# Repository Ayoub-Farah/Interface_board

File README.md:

# Obsidian

## Description

Obsidian is a FPGA carrier board in development, designed to interface with ADC and DAC devices,
either stand-alone or as an I/O expansion board for [Marble](https://github.com/BerkeleyLab/Marble).

The design files here were created with [KiCad](https://www.kicad.org/) version 9.0.0-rc3.

## Major Parts

- Xilinx XC7A50T-1CSG325C FPGA

## Credits

## License

---

## Project status

### Included features

- [ ] Arduino shield compatible, like the Digilent Arty
- [ ] SPI flash boot
- [ ] DDR3 memory chip
- [ ] FTDI USB interface
- [ ] 2 direct LEDs
- [ ] 1 GigE port (PoE?)
- [ ] 6 Pmod ports (3.3V)
- [ ] MS5351M or SI5351A or similar for GTP frequency reference
- [ ] USB-C (single USB cable)
- [ ] 4 x SFP
- [ ] I2C or 1-Wire chip for serial number / ROM
- [ ] White Rabbit compatibility

### High speed links

The 7A50T-1CSG325C has 4 x GTP lanes, capable of 3.75 Gbaud.
The primary use-case involves attaching one of those to a Marble over fiber.

The two MGTREFCLK signals are the direct White-Rabbit 125 MHz TCVCXO
and the configurable MS5351M output.

### Wishlist

- [ ] Standardized board size for good case options: Mini-ATX (150 x 150 mm)? Pico-ATX?

### User I/O Pins
- 48 pins for 6 x Pmod
- 49 pins for DDR3 (equivalent to Arty and Marble-Mini)
- 13 pins for RGMII (including reset pin)
- 2 Ethernet PHY MDIO
- 4 pins for White Rabbit DAC (can attach LEDs to 2 x SYNC pins?)
- 1 or more clock input (not counting MGTREFCLK)
- 2 pins for I2C
- 14 pins for Arduino digital IO
- 8 pins for Arduino 4 analog channels
- 2 pins USB UART
- 3 pins SPI flash boot (not counting CCLK in bank 0)

total 146 so far, out of 150 possible with 7A50T-1CSG325C

## Copyright

Obsidian A35 Copyright (c) 2025, The Regents of the University of California, through Lawrence Berkeley National Laboratory (subject to receipt of any required approvals from the U.S. Department of Energy). All rights reserved.

This documentation describes Obsidian A35 and is licensed under the CERN Open Hardware License v 2.0 - Permissive.

NOTICE. This documentation was developed under funding from the U.S. Department of Energy and the U.S. Government consequently retains certain rights. As such, the U.S. Government has been granted for itself and others acting on its behalf a paid-up, nonexclusive, irrevocable, worldwide license in the documentation to reproduce, distribute copies to the public, prepare derivative works, and perform publicly and display publicly, and to permit others to do so.

You may redistribute and modify this documentation under the terms of the CERN OHL v. 2.0 - Permissive (see [CERN-OHL-P-2.0](https://spdx.org/licenses/CERN-OHL-P-2.0.html) for terms and conditions). THIS DOCUMENTATION IS PROVIDED BY THE COPYRIGHT HOLDERS AND CONTRIBUTORS "AS IS" AND ANY EXPRESS OR IMPLIED WARRANTIES, INCLUDING, BUT NOT LIMITED TO, THE IMPLIED WARRANTIES OF MERCHANTABILITY AND FITNESS FOR A PARTICULAR PURPOSE ARE DISCLAIMED. IN NO EVENT SHALL THE COPYRIGHT OWNER OR CONTRIBUTORS BE LIABLE FOR ANY DIRECT, INDIRECT, INCIDENTAL, SPECIAL, EXEMPLARY, OR CONSEQUENTIAL DAMAGES (INCLUDING, BUT NOT LIMITED TO, PROCUREMENT OF SUBSTITUTE GOODS OR SERVICES; LOSS OF USE, DATA, OR PROFITS; OR BUSINESS INTERRUPTION) HOWEVER CAUSED AND ON ANY THEORY OF LIABILITY, WHETHER IN CONTRACT, STRICT LIABILITY, OR TORT (INCLUDING NEGLIGENCE OR OTHERWISE) ARISING IN ANY WAY OUT OF THE USE OF THIS SOFTWARE, EVEN IF ADVISED OF THE POSSIBILITY OF SUCH DAMAGE. Please see the CERN OHL v. 2.0 for applicable conditions.

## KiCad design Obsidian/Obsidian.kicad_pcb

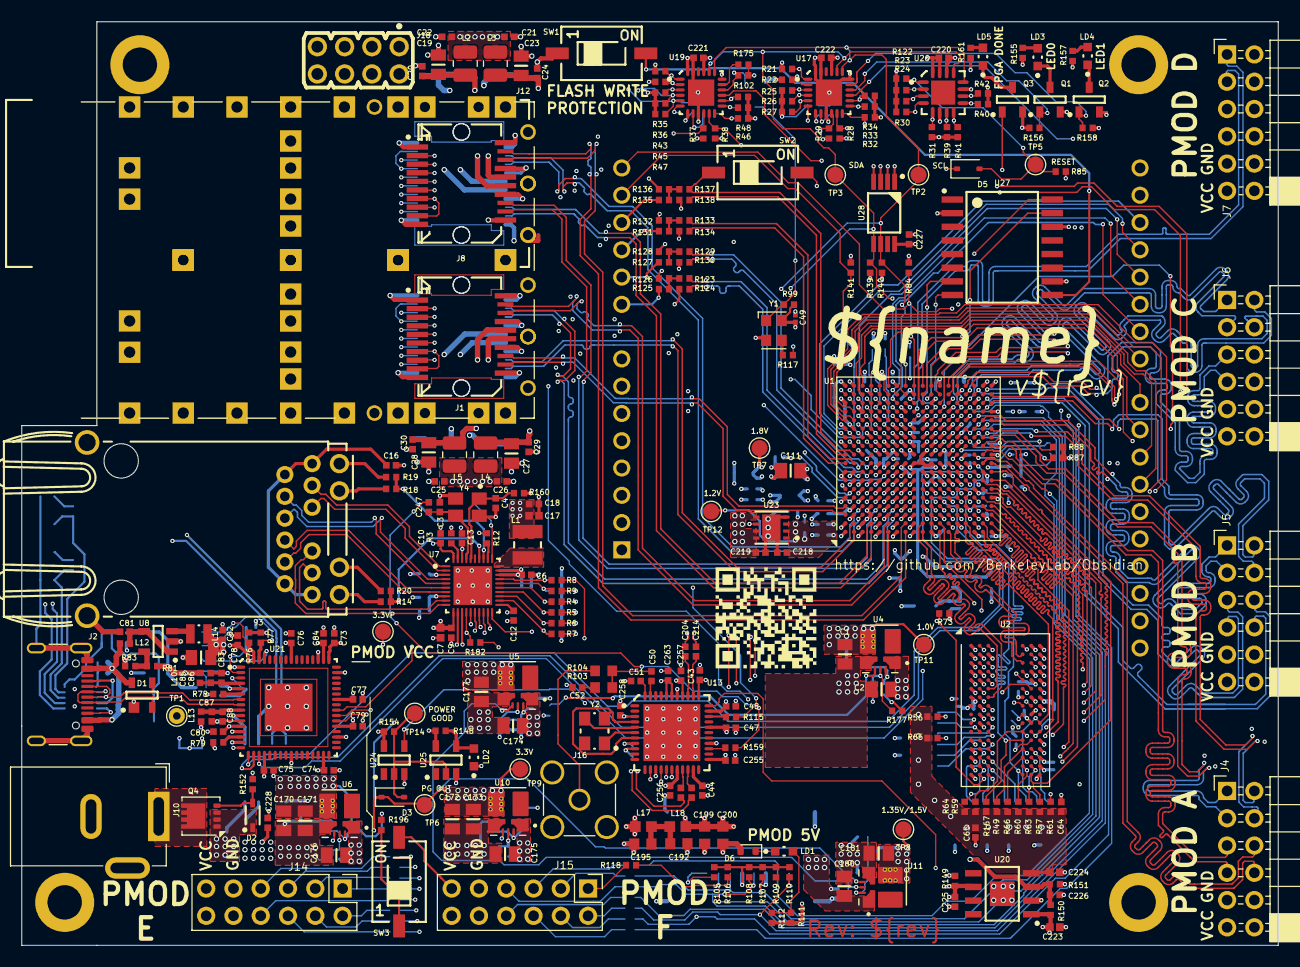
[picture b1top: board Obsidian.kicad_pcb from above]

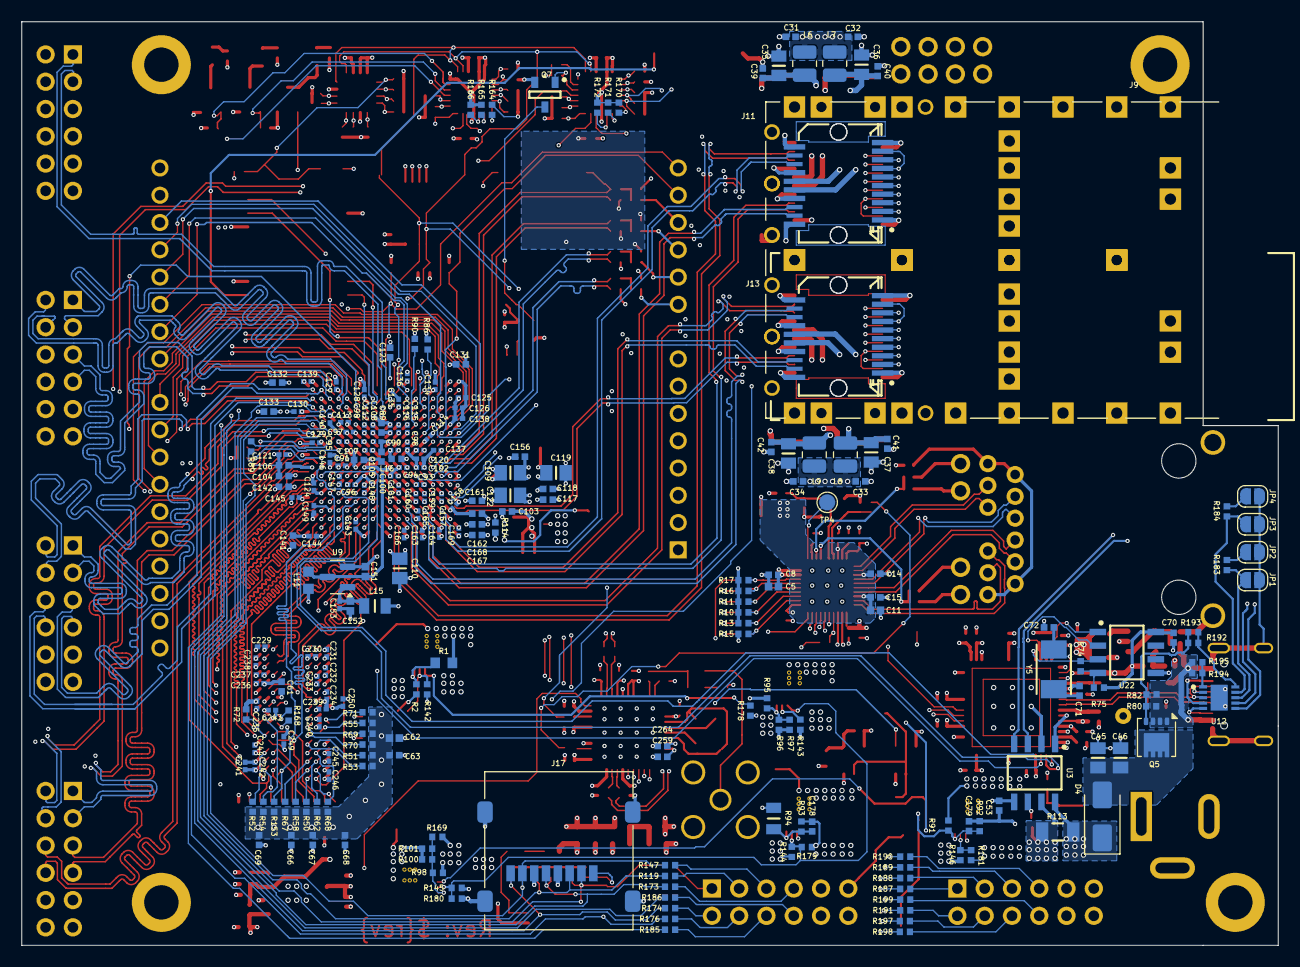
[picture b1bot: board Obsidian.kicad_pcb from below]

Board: 8 copper layers, 117.0 x 86.0 mm, 521 parts (238 on the bottom side), 370 nets.

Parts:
A1: Arduino_UNO_R3
B1, B2, B3, B4: PLATED_HOLE3.2_PAD5.5; MTG320_550
C1, C19, C23, C27, C28, C35, C36, C37, C38, C83, C170, C171, C172, C173, C177, C181: CC0805_22UF_16V_10%_X5R; CAPC2012X135N
C2, C45, C46, C174, C175, C176, C180: CC0805_10UF_25V_10%_X5R; CAPC2012X95N
C3, C4, C71, C72: CC0402_27PF_50V_5%_C0G; CAPC1005X55N
C5, C7, C11, C17, C62, C151, C152, C223, C224: CC0402_10UF_6.3V_20%_X5R; CAPC1005X70N
C6, C8, C9, C10, C12, C13, C14, C15, C16, C18, C20, C21, C22, C24, C25, C26, C29, C30, C31, C32, C33, C34, C39, C40, C41, C42, C50, C51, C52, C53, C63, C64, C65, C66, C67, C68, C69, C70, C74, C75, C76, C77, C78, C79, C80, C82, C84, C86, C88, C204, C205, C213, C214, C220, C221, C222, C225, C226, C227, C228, C247: CC0402_100NF_50V_10%_X7R; CAPC1005X55N
C43, C44, C47, C48, C255, C256, C257, C258, C259, C263, C264: CC0402_1UF_25V_10%_X5R; CAPC1005X55N
C49, C154, C157, C158, C159, C160, C163, C164, C165, C166, C169, C249, C250: CC0201_100NF_6.3V_10%_X5R; CAPC0603X33N
C61, C73, C81, C85, C87, C103, C104, C105, C106, C107, C108, C117, C118, C123, C131, C132, C133, C141, C142, C156, C161, C162, C167, C168, C218, C219: CC0402_4.7UF_16V_20%_X5R; CAPC1005X55N
C89, C90, C91, C92, C93, C94, C95, C96, C113, C114, C115, C116, C120, C124, C125, C126, C127, C134, C135, C136, C137, C143, C144, C145, C146, C153, C155, C245, C246: CC0201_470NF_4V_20%_X5R; CAPC0603X33N
C97, C98, C99, C100, C101, C102, C112, C121, C128, C129, C130, C138, C139, C140, C147, C148, C149, C150, C229, C230, C231, C232, C233, C234, C235, C236, C237, C238, C239, C240, C241, C242, C243, C244: CC0201_47NF_6.3V_10%_X5R; CAPC0603X33N
C109, C110, C111, C119, C122: CC0805_100UF_6.3V_20%_X5R; CAPC2012X145N
C178, C179: CC0402_22PF_50V_5%_C0G; CAPC1005X55N
C192, C195, C199, C200: CC0603_22UF_6.3V_20%_X5R; CAPC1709X100N
D1: PRTR5V0U2X; SOT190P230X110-4N
D2: MM3Z12VB; SODFL2513X100N
D3, D5: BAS316; D_SOD-323
D4: SS38; D_SMA
D6: DZ2S030X0L; D_SOD-523
J1, J11: TYCO_1888247-1; TYCO_1367073-1
J2: USB_C_Receptacle_USB2.0_16P; USB_C_Receptacle_GCT_USB4105-xx-A_16P_TopMnt_Horizontal
J3: BELFUSE_0826-1G1T-43-F; BEL_0826-1G1T-43-F
J4, J5, J6, J7: Conn_02x06_Top_Bottom; PinSocket_2x06_P2.54mm_Horizontal_PMOD
J8, J9: 2180739-1; TE_2180739-1
J10: Barrel_Jack_Switch; BarrelJack_GCT_DCJ200-10-A_Horizontal
J12, J13: TYCO_1888247-1
J14, J15: Conn_02x06_Top_Bottom; PinSocket_2x06_P2.54mm_Vertical_PMOD
J16: Conn_Coaxial; SMA_Amphenol_901-144_Vertical
J17: Micro_SD_Card; microSD_HC_Molex_47219-2001
J18: Header 8; WURTH_61300821121
JP1, JP2, JP3, JP4: SolderJumper_2_Open; SolderJumper-2_P1.3mm_Open_RoundedPad1.0x1.5mm
L1: IND_2.2UH_20%_BOURNS_SRP3212; IND_BOURNS_SRP3212
L2, L3, L4, L5, L6, L7, L8, L9: 4.7 uH; L_1008_2520Metric
L10, L12, L13: IND0402_MURATA_BLM15PX121SN1D; INDC1005X55N
L11: IND0603_MURATA_BLM18AG601SN1; INDC1608X95N
L14: IND_2.2UH_20%_WURTH_WE-PMCI_74479276222C; IND_WURTH_WE-PMCI_0806LR
L15: IND0805_TDK_MLZ2012M150WT000; INDC2013X145N
L16: IND0402_MURATA_BLM15HB221SN1; INDC1005X55N
L17, L18: IND0603_MURATA_BLM18SG121TN1D; INDC1608X65N
LD1, LD2, LD3, LD4, LD5: LED_KINGBRIGHT_KPH-1608CGCK
Q1, Q2, Q3, Q7: BSS138LT1G; SOT95P240X110-3N
Q4, Q5: DMP3013SFV; Diodes_PowerDI3333-8
R1: R0603_6K65_0.1%_0.063W_10PPM; RESC1608X55N
R2, R75, R76, R77, R81, R98, R99, R102, R105, R106, R107, R108, R109, R110, R156, R158, R183, R184, R192, R193: R0402_10K_1%_0.0625W_100PPM; RESC1005X40N
R3: R0402_2K49_1%_0.063W_100PPM; RESC1005X40N
R4, R5, R6, R7, R8, R9, R194, R195: R0402_22R_1%_0.0625W_100PPM; RESC1005X40N
R10, R11, R12, R13, R14, R15, R16, R17, R18, R21, R22, R23, R24, R25, R26, R27, R28, R29, R30, R31, R32, R33, R34, R35, R36, R37, R38, R39, R40, R41, R42, R43, R44, R45, R46, R47, R48, R73, R79, R85, R86, R87, R122, R139, R140, R141, R148, R155, R157, R161, R182: R0402_4K7_1%_0.0625W_100PPM; RESC1005X40N
R19, R20, R118, R119, R147, R173, R174, R176, R185, R186, R187, R188, R189, R190, R191, R197, R198, R199: R0402_330R_1%_0.0625W_100PPM; RESC1005X40N
R49, R50, R51, R52, R53, R54, R55, R56, R57, R58, R59, R60, R61, R62, R63, R64, R65, R66, R67, R68, R69, R70, R71, R111, R112, R153, R159, R167: R0402_40R2_1%_0.0625W_100PPM; RESC1005X40N
R72: R0402_240R_1%_0.0625W_100PPM; RESC1005X40N
R74, R83: R0402_2K2_1%_0.0625W_100PPM; RESC1005X40N
R78, R152, R169, R177, R178, R179, R180, R181: R0402_12K_1%_0.0625W_100PPM; RESC1005X40N
R80, R82, R154, R164, R165, R166, R170, R171, R172, R175: R0402_100K_1%_0.0625W_100PPM; RESC1005X40N
R84, R88, R89, R90, R126, R128, R132, R136, R149, R150, R151: R0402_1K_1%_0.0625W_100PPM; RESC1005X40N
R91: R0402_220K_1%_0.0625W_100PPM; RESC1005X40N
R92, R93, R95, R96, R97, R100, R101, R142, R143, R144, R145, R146: R0402_30K_1%_0.0625W_100PPM; RESC1005X40N
R94: R0805_135K_0.1%_0.1W_25PPM_KOA_RN73R2ATTD1353B25; RESC2012X60N
R103: R0603_845R_0.1%_0.063W_10PPM; RESC1608X55N
R104: R0603_267R_0.1%_0.063W_10PPM; RESC1608X55N
R113: 0R01; RESC3216X65N
R114, R115, R117: R0402_100R_1%_0.1W_100PPM; RESC1005X40N
R123, R129, R133, R137: R0402_140R_1%_0.0625W_100PPM; RESC1005X40N
R124, R130, R134, R138: R0402_845R_0.1%_0.063W_25PPM; RESC1005X40N
R125, R127, R131, R135: R0402_2K32_1%_0.0625W_100PPM; RESC1005X40N
R160: R0402_0R_JUMPER; RESC1005X40N
R168: R0402_80R6_1%_0.1W_100PPM; RESC1005X40N
R196: R0402_360K_1%_0.0625W_100PPM; RESC1005X40N
SW1, SW2, SW3: SW_DIP_x01; SW_OMRON_A6SN-1101
TP1: TestPoint; TestPoint_THTPad_D1.5mm_Drill0.7mm
TP2, TP3, TP4, TP5, TP6, TP7, TP8, TP9, TP10, TP11, TP12, TP14: TestPoint; TestPoint_Pad_D1.5mm
U1: XC7A35T-CSG325; Xilinx_CSG325
U2: MT41K512M16HA-125_E / MT41K512M16VRP-107 IT:P; FBGA-96_8x14mm_Layout9x16_P0.8mm
U3: INA219AID; SOIC127P600X175-8N
U4, U5, U6, U10, U11: TPSM863257RDXR; VREG_TPSM863257RDXR
U7: RTL8211F-CG; QFN40P500X500X80-41N-S360
U8: TLV62565DBV; SOT95P280X145-5N
U9: REF3012; SOT-23
U12: HUSB238; SON50P300X300X80-11N-R160X240
U13: SI5340B-D-GM; QFN50P700X700X90-45N-S530
U17, U19: TCA9535RTWR; QFN50P400X400X80-25N-S245
U20: RT9045AGSP / AP2303; SOIC127P600X168-9N-S230
U21: FT2232HQ; QFN50P900X900X100-65N-S445
U22: 93C46B-I_SN; SOIC127P600X175-8N
U23: NCV59801CML120TCG; SON65P300X300X100-9N-R170X245
U24, U25: SN74LVC1G07DBV; SOT95P280X145-5N
U26: PCA9546ARGV; QFN65P400X400X100-17N-S225
U27: S25FL128SAGMFI001; SOIC127P1030X265-16N
U28: 24AA256UID-I_ST; SOP65P640X120-8N
Y1: KC2520Z25.0000C1KX00; Oscillator_SMD_Kyocera_KC2520Z-4Pin_2.5x2.0mm
Y2: XTAL_48MHZ_KYOCERA_CX3225SB48000D0FPJC1; XTAL_KYOCERA_CX3225SB
Y4: XTAL_25MHZ_EPSON_TSX-3225_25.0000MF10Z-AC; XTAL_EPSON_TSX-3225
Y5: XTAL_12MHZ_TXC_7A-12.000MAAJ-T; XTAL_TXC_7A

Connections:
1V8USB: C73.1, C78.2, C79.2, C80.2, U21.12 (VCORE), U21.37 (VCORE), U21.49 (VREGOUT), U21.64 (VCORE)
25M_CLK_DIS: Q7.1 (G), R102.2, U19.16
+1V0: C1.2, C89.2, C90.2, C91.2, C92.2, C93.2, C94.2, C95.2, C96.2, C97.2, C98.2, C99.2, C100.2, C101.2, C102.2, C103.2, C104.2, C105.2, C106.2, C107.2, C108.2, C109.2, C110.2, C111.2, C120.2, C121.2, C122.2, C157.2, C158.2, C159.2, C160.2, C161.2, C162.2, R1.2, TP11.1, U1.B4 (MGTAVCC), U1.C5 (MGTAVCC), U1.E5 (MGTAVCC), U1.F5 (MGTAVCC), U1.F7 (VCCINT), U1.F9 (VCCINT), U1.F11 (VCCBRAM), U1.G8 (VCCINT), U1.G10 (VCCBRAM), U1.H7 (VCCINT), U1.H9 (VCCINT), U1.H11 (VCCBRAM), U1.J8 (VCCINT), U1.J12 (VCCINT), U1.K7 (VCCINT), U1.K11 (VCCINT), U1.L8 (VCCINT), U1.L12 (VCCINT), U1.M7 (VCCINT), U1.M11 (VCCINT), U1.N8 (VCCINT), U1.N10 (VCCINT), U1.N12 (VCCINT), U1.P9 (VCCINT), U1.P11 (VCCINT), U4.3 (VOUT)
+1V2: C163.2, C164.2, C165.2, C166.2, C167.2, C168.2, C169.2, C218.2, R114.2, TP12.1, U1.A2 (MGTAVTT), U1.C1 (MGTAVTT), U1.E1 (MGTAVTT), U1.F3 (MGTAVTT), U1.G2 (MGTAVTT), U23.1 (OUT_1), U23.2 (OUT_2), U23.3 (FB/SNS)
+1V8: C44.2, C48.2, C112.2, C113.2, C114.2, C115.2, C116.2, C117.2, C118.2, C119.2, C156.2, C177.2, C219.2, C263.2, L16.1, R95.2, TP7.1, U1.E11 (VCCBATT_0), U1.G12 (VCCAUX), U1.H13 (VCCAUX), U1.K13 (VCCAUX), U1.M13 (VCCAUX), U1.P13 (VCCAUX), U5.3 (VOUT), U13.21 (VDD), U13.32 (VDD), U13.39 (VDD), U13.40 (VDD), U23.5 (EN), U23.7 (IN_1), U23.8 (IN_2)
+3V3: A1.4 (3V3), C5.2, C6.2, C7.2, C8.2, C9.2, C10.2, C21.2, C22.2, C25.2, C26.2, C31.2, C32.2, C33.2, C34.2, C49.1, C53.2, C74.2, C75.2, C76.2, C77.2, C123.2, C124.2, C125.2, C126.2, C127.2, C128.2, C129.2, C130.2, C131.2, C132.2, C133.2, C134.2, C135.2, C136.2, C137.2, C138.2, C139.2, C140.2, C146.2, C150.2, C172.2, C173.2, C220.2, C221.2, C222.2, C225.2, C227.2, J17.4 (VDD), J18.3, L2.1, L3.1, L4.1, L5.1, L6.1, L7.1, L8.1, L9.1, L15.1, L17.1, R12.2, R15.2, R21.2, R23.2, R24.2, R25.2, R26.2, R27.2, R28.2, R30.2, R31.2, R32.2, R33.2, R34.2, R35.2, R37.2, R39.2, R40.2, R41.2, R42.2, R43.2, R44.2, R45.2, R46.2, R47.2, R48.2, R84.1, R85.2, R86.2, R87.2, R88.2, R94.1, R99.2, R105.1, R106.1, R107.1, R108.1, R109.1, R110.1, R122.2, R139.2, R140.2, R141.2, R148.2, R149.2, R154.1, R155.2, R157.2, R161.2, R164.1, R182.2, TP9.1, U1.A16 (VCCO_15), U1.B13 (VCCO_15), U1.C10 (VCCO_15), U1.D17 (VCCO_15), U1.E10 (VCCO_0), U1.E14 (VCCO_15), U1.G18 (VCCO_15), U1.H15 (VCCO_15), U1.L16 (VCCO_14), U1.P17 (VCCO_14), U1.R10 (VCCO_0), U1.R14 (VCCO_14), U1.T11 (VCCO_14), U1.U8 (VCCO_14), U1.U18 (VCCO_14), U1.V15 (VCCO_14), U3.5 (VS), U7.11 (AVDD33), U7.28 (DVDD_RG), U7.29 (DVDD33), U7.40 (AVDD33), U10.3 (VOUT), U17.21 (VCC), U19.18 (A0), U19.21 (VCC), U20.6 (VCNTL), U21.20 (VCCIO), U21.31 (VCCIO), U21.42 (VCCIO), U21.56 (VCCIO), U24.5 (VCC), U25.5 (VCC), U26.14 (VCC), U27.2 (VCC), U27.14 (VIO/RFU), U28.8 (VCC), Y1.4 (VCC)
+3V3_CLEAN: C43.2, C47.2, C199.1, C200.1, C255.2, C256.2, C257.2, C258.2, C259.2, C264.2, L18.2, U13.3 (IN_SEL0), U13.8 (VDDA), U13.9 (VDDA), U13.18 (VDDO0), U13.23 (VDDO1), U13.29 (VDDO2), U13.34 (VDDO3), U13.37 (IN_SEL1)
+3V3_P: A1.2 (IOREF), A1.5 (+5V), C170.2, C171.2, J4.6, J4.12, J5.6, J5.12, J6.6, J6.12, J7.6, J7.12, J14.6, J14.12, J15.6, J15.12, R91.2, R111.2, R112.2, SW3.2, TP10.1, U6.3 (VOUT)
+3V3_USB: C70.2, C82.2, C83.2, C84.1, L10.1, L13.1, L14.2, R75.1, R76.2, R77.2, R79.2, R81.2, TP1.1, U21.50 (VREGIN), U22.8 (VCC)
+12V: A1.8 (VIN), C2.2, C174.2, C175.2, C176.2, C180.2, C228.2, J18.1, R113.2, R142.2, R143.2, R144.2, R145.2, R146.2, U3.7 (VIN-), U4.1 (VIN), U5.1 (VIN), U6.1 (VIN), U10.1 (VIN), U11.1 (VIN)
/Arduino/A0: A1.9 (A0), R125.1
/Arduino/A1: A1.10 (A1), R127.1
/Arduino/A2: A1.11 (A2), R131.1
/Arduino/A3: A1.12 (A3), R135.1
/Clock-WR/REFCLK0_N: C214.2, U13.35 (~OUT3)
/Clock-WR/REFCLK0_P: C204.2, U13.36 (OUT3)
/Clock-WR/WRCLK0_N: C213.2, U13.19 (~OUT0)
/Clock-WR/WRCLK0_P: C205.2, U13.20 (OUT0)
/Ethernet/LED0: R12.1, U7.32 (LED0/CFG_EXT)
/Ethernet/LED1: R18.2, R19.1, U7.33 (LED1/CFG_LDO0)
/Ethernet/LED2: R14.2, R20.1, U7.34 (LED2/CFG_LDO1)
/Ethernet/MDI0_N: J3.10 (TRD1-), U7.2 (MDIN0)
/Ethernet/MDI0_P: J3.11 (TRD1+), U7.1 (MDIP0)
/Ethernet/MDI1_N: J3.5 (TRD2-), U7.5 (MDIN1)
/Ethernet/MDI1_P: J3.4 (TRD2+), U7.4 (MDIP1)
/Ethernet/MDI2_N: J3.2 (TRD3-), U7.7 (MDIN2)
/Ethernet/MDI2_P: J3.3 (TRD3+), U7.6 (MDIP2)
/Ethernet/MDI3_N: J3.9 (TRD4-), U7.10 (MDIN3)
/Ethernet/MDI3_P: J3.8 (TRD4+), U7.9 (MDIP3)
/Ethernet/RX0_T: R4.2, R11.2, U7.25 (RXD0/RXDLY)
/Ethernet/RX1_T: R5.2, R10.2, U7.24 (RXD1/TXDLY)
/Ethernet/RX2_T: R6.2, R13.2, U7.23 (RXD2/PLLOFF)
/Ethernet/RX3_T: R7.2, R15.1, U7.22 (RXD3/PHYAD0)
/Ethernet/RXCTL_T: R9.2, R16.2, U7.26 (RXCTL/PHYAD2)
/Ethernet/RXC_T: R8.2, R17.2, U7.27 (RXC/PHYAD1)
/FPGA_MISC/CCLK: U1.E8 (CCLK_0), U27.16 (SCK)
/FPGA_MISC/VREF: C151.2, C154.2, U1.L10 (VREFP_0), U9.2 (OUT)
/SFP/I2C_SFP0_SCL: J12.5 (SCL), R24.1, U26.3 (SC0)
/SFP/I2C_SFP0_SDA: J12.4 (SDA), R23.1, U26.2 (SD0)
/SFP/I2C_SFP1_SCL: J1.5 (SCL), R31.1, U26.5 (SC1)
/SFP/I2C_SFP1_SDA: J1.4 (SDA), R30.1, U26.4 (SD1)
/SFP/I2C_SFP2_SCL: J11.5 (SCL), R41.1, U26.8 (SC2)
/SFP/I2C_SFP2_SDA: J11.4 (SDA), R39.1, U26.7 (SD2)
/SFP/I2C_SFP3_SCL: J13.5 (SCL), R42.1, U26.10 (SC3)
/SFP/I2C_SFP3_SDA: J13.4 (SDA), R40.1, U26.9 (SD3)
/SFP/RS0: J12.7 (RS0), J12.9 (RS1), R26.1, U17.4 (P03)
/SFP/RS1: J1.7 (RS0), J1.9 (RS1), R33.1, U17.13
/SFP/RS2: J11.7 (RS0), J11.9 (RS1), R45.1, U19.4 (P03)
/SFP/RS3: J13.7 (RS0), J13.9 (RS1), R46.1, U19.13
/SFP/SFP0_DEF0: J12.6 (MOD_ABS), R25.1, U17.3 (P02)
/SFP/SFP0_LOS: J12.8 (LOS), R27.1, U17.5 (P04)
/SFP/SFP0_TX_DIS: J12.3 (TX_DISABLE), R22.2, U17.2 (P01)
/SFP/SFP0_TX_FAULT: J12.2 (TX_FAULT), R21.1, U17.1 (P00)
/SFP/SFP1_DEF0: J1.6 (MOD_ABS), R32.1, U17.12
/SFP/SFP1_LOS: J1.8 (LOS), R34.1, U17.14
/SFP/SFP1_TX_DIS: J1.3 (TX_DISABLE), R29.2, U17.11
/SFP/SFP1_TX_FAULT: J1.2 (TX_FAULT), R28.1, U17.10
/SFP/SFP2_DEF0: J11.6 (MOD_ABS), R43.1, U19.3 (P02)
/SFP/SFP2_LOS: J11.8 (LOS), R47.1, U19.5 (P04)
/SFP/SFP2_TX_DIS: J11.3 (TX_DISABLE), R36.2, U19.2 (P01)
/SFP/SFP2_TX_FAULT: J11.2 (TX_FAULT), R35.1, U19.1 (P00)
/SFP/SFP3_DEF0: J13.6 (MOD_ABS), R44.1, U19.12
/SFP/SFP3_LOS: J13.8 (LOS), R48.1, U19.14
/SFP/SFP3_TX_DIS: J13.3 (TX_DISABLE), R38.2, U19.11
/SFP/SFP3_TX_FAULT: J13.2 (TX_FAULT), R37.1, U19.10
/USB/CC1: J2.A5 (CC1), U12.4 (CC1)
/USB/CC2: J2.B5 (CC2), U12.5 (CC2)
/USB/USB_N: D1.3 (I/O2), J2.A7 (D-), J2.B7 (D-), U12.3 (D-), U21.7 (DM)
/USB/USB_P: D1.2 (I/O1), J2.A6 (D+), J2.B6 (D+), U12.2 (D+), U21.8 (DP)
AD0_N: R124.2, U1.C8 (IO_L1N_T0_AD0N_15)
AD0_P: R123.2, U1.D8 (IO_L1P_T0_AD0P_15)
AD1_N: R134.2, U1.A9 (IO_L3N_T0_DQS_AD1N_15)
AD1_P: R133.2, U1.B9 (IO_L3P_T0_DQS_AD1P_15)
AD8_N: R130.2, U1.C9 (IO_L2N_T0_AD8N_15)
AD8_P: R129.2, U1.D9 (IO_L2P_T0_AD8P_15)
AD9_N: R138.2, U1.A10 (IO_L5N_T0_AD9N_15)
AD9_P: R137.2, SW2.1, U1.B10 (IO_L5P_T0_AD9P_15)
ARDUINO_D0: A1.15 (D0/RX), U1.G14 (IO_L22P_T3_A17_15)
ARDUINO_D1: A1.16 (D1/TX), U1.H16 (IO_L20P_T3_A20_15)
ARDUINO_D2: A1.17 (D2), U1.A12 (IO_L7N_T1_AD2N_15)
ARDUINO_D3: A1.18 (D3), U1.B12 (IO_L7P_T1_AD2P_15)
ARDUINO_D4: A1.19 (D4), U1.C14 (IO_L9P_T1_DQS_AD3P_15)
ARDUINO_D5: A1.20 (D5), U1.G17 (IO_L19P_T3_A22_15)
ARDUINO_D6: A1.21 (D6), U1.G16 (IO_L20N_T3_A19_15)
ARDUINO_D7: A1.22 (D7), U1.A15 (IO_L10N_T1_AD11N_15)
ARDUINO_D8: A1.23 (D8), U1.C18 (IO_L18N_T2_A23_15)
ARDUINO_D9: A1.24 (D9), U1.F18 (IO_L19N_T3_A21_VREF_15)
ARDUINO_D10: A1.25 (D10), U1.C17 (IO_L18P_T2_A24_15)
ARDUINO_D11: A1.26 (D11), U1.B15 (IO_L9N_T1_DQS_AD3N_15)
ARDUINO_D12: A1.27 (D12), U1.B14 (IO_L10P_T1_AD11P_15)
ARDUINO_D13: A1.28 (D13), U1.A14 (IO_L8N_T1_AD10N_15)
CFG_DIN: U1.L17 (IO_L1N_T0_D01_DIN_14), U27.8 (SO/IO1)
CFG_FCS: U1.L15 (IO_L6P_T0_FCS_B_14), U27.7 (~CS)
CFG_MOSI: U1.K16 (IO_L1P_T0_D00_MOSI_14), U27.15 (SI/IO0)
CLK2: R117.2, U1.E15 (IO_L13P_T2_MRCC_15)
CLK20_VCXO: R115.2, U1.D13 (IO_L11P_T1_SRCC_15)
CLK_25MHZ: C247.2, R159.2
DDR3_A0: R65.1, U1.U2 (IO_L15P_T2_DQS_34), U2.N3 (A0)
DDR3_A1: R66.1, U1.V3 (IO_L16P_T2_34), U2.P7 (A1)
DDR3_A2: R67.1, U1.R7 (IO_L22P_T3_34), U2.P3 (A2)
DDR3_A3: R68.1, U1.P6 (IO_L19P_T3_34), U2.N2 (A3)
DDR3_A4: R61.1, U1.V2 (IO_L16N_T2_34), U2.P8 (A4)
DDR3_A5: R62.1, U1.V4 (IO_L18N_T2_34), U2.P2 (A5)
DDR3_A6: R63.1, U1.V7 (IO_L24N_T3_34), U2.R8 (A6)
DDR3_A7: R64.1, U1.T7 (IO_L22N_T3_34), U2.R2 (A7)
DDR3_A8: R57.1, U1.V8 (IO_L24P_T3_34), U2.T8 (A8)
DDR3_A9: R58.1, U1.U4 (IO_L18P_T2_34), U2.R3 (A9)
DDR3_A10: R59.1, U1.U1 (IO_L15N_T2_DQS_34), U2.L7 (A10/AP)
DDR3_A11: R60.1, U1.U7 (IO_L23P_T3_34), U2.R7 (A11)
DDR3_A12: R49.1, U1.U6 (IO_L20P_T3_34), U2.N7 (A12/~BC)
DDR3_A13: R50.1, U1.U5 (IO_L20N_T3_34), U2.T3 (A13)
DDR3_A14: R153.1, U1.R6 (IO_25_34), U2.T7 (A14)
DDR3_A15: R167.1, U1.M5 (IO_L6N_T0_VREF_34), U2.M7 (A15)
DDR3_BA0: R51.1, U1.T3 (IO_L17N_T2_34), U2.M2 (BA0)
DDR3_BA1: R52.1, U1.V6 (IO_L23N_T3_34), U2.N8 (BA1)
DDR3_BA2: R53.1, U1.R2 (IO_L13P_T2_MRCC_34), U2.M3 (BA2)
DDR3_CAS: R69.1, U1.T2 (IO_L14N_T2_SRCC_34), U2.K3 (~CAS)
DDR3_CE: R55.1, U1.P5 (IO_L19N_T3_VREF_34), U2.L2 (~CS)
DDR3_CKE0: R54.1, U1.R1 (IO_L13N_T2_MRCC_34), U2.K9 (CKE)
DDR3_CLK_N: R168.1, U1.T5 (IO_L21N_T3_DQS_34), U2.K7 (~CK)
DDR3_CLK_P: R168.2, U1.R5 (IO_L21P_T3_DQS_34), U2.J7 (CK)
DDR3_D0: U1.K3 (IO_L4P_T0_34), U2.E3 (DQ0)
DDR3_D1: U1.L4 (IO_L5P_T0_34), U2.F7 (DQ1)
DDR3_D2: U1.K5 (IO_L1N_T0_34), U2.F2 (DQ2)
DDR3_D3: U1.K6 (IO_L1P_T0_34), U2.F8 (DQ3)
DDR3_D4: U1.J4 (IO_L2N_T0_34), U2.H3 (DQ4)
DDR3_D5: U1.L2 (IO_L4N_T0_34), U2.H8 (DQ5)
DDR3_D6: U1.J5 (IO_L2P_T0_34), U2.G2 (DQ6)
DDR3_D7: U1.L3 (IO_L5N_T0_34), U2.H7 (DQ7)
DDR3_D8: U1.N3 (IO_L11P_T1_SRCC_34), U2.D7 (DQ8)
DDR3_D9: U1.M1 (IO_L7N_T1_34), U2.C3 (DQ9)
DDR3_D10: U1.N2 (IO_L11N_T1_SRCC_34), U2.C8 (DQ10)
DDR3_D11: U1.M4 (IO_L10P_T1_34), U2.C2 (DQ11)
DDR3_D12: U1.N6 (IO_L8N_T1_34), U2.A7 (DQ12)
DDR3_D13: U1.M2 (IO_L7P_T1_34), U2.A2 (DQ13)
DDR3_D14: U1.P4 (IO_L12P_T1_MRCC_34), U2.B8 (DQ14)
DDR3_D15: U1.N4 (IO_L10N_T1_34), U2.A3 (DQ15)
DDR3_DM0: U1.L5 (IO_L6P_T0_34), U2.E7 (LDM)
DDR3_DM1: U1.M6 (IO_L8P_T1_34), U2.D3 (UDM)
DDR3_DQS0_N: U1.K1 (IO_L3N_T0_DQS_34), U2.G3 (~LDQS)
DDR3_DQS0_P: U1.K2 (IO_L3P_T0_DQS_34), U2.F3 (LDQS)
DDR3_DQS1_N: U1.P1 (IO_L9N_T1_DQS_34), U2.B7 (~UDQS)
DDR3_DQS1_P: U1.N1 (IO_L9P_T1_DQS_34), U2.C7 (UDQS)
DDR3_ODT: R71.1, U1.P3 (IO_L12N_T1_MRCC_34), U2.K1 (ODT)
DDR3_RAS: R56.1, U1.R3 (IO_L14P_T2_SRCC_34), U2.J3 (~RAS)
DDR3_RST: R73.2, U1.J6 (IO_0_34), U2.T2 (~RESET)
DDR3_WE: R70.1, U1.T4 (IO_L17P_T2_34), U2.L3 (~WE)
DDRVCC: C61.2, C141.2, C142.2, C143.2, C144.2, C145.2, C147.2, C148.2, C149.2, C181.2, C223.2, C229.2, C230.2, C231.2, C232.2, C233.2, C234.2, C235.2, C236.2, C237.2, C238.2, C239.2, C240.2, C241.2, C242.2, C243.2, C244.2, C245.2, C246.2, R100.2, R101.2, R150.2, TP8.1, U1.L6 (VCCO_34), U1.M3 (VCCO_34), U1.P7 (VCCO_34), U1.R4 (VCCO_34), U1.T1 (VCCO_34), U1.V5 (VCCO_34), U2.A1 (VDDQ), U2.A8 (VDDQ), U2.B2 (VDD), U2.C1 (VDDQ), U2.C9 (VDDQ), U2.D2 (VDDQ), U2.D9 (VDD), U2.E9 (VDDQ), U2.F1 (VDDQ), U2.G7 (VDD), U2.H2 (VDDQ), U2.H9 (VDDQ), U2.K2 (VDD), U2.K8 (VDD), U2.N1 (VDD), U2.N9 (VDD), U2.R1 (VDD), U2.R9 (VDD), U11.3 (VOUT), U20.1 (VIN)
DDRVREF: C226.2, C249.2, C250.2, R150.1, R151.2, U2.H1 (VREFDQ), U2.M8 (VREFCA), U20.3 (~VREFEN~{})
DDRVTT: C62.1, C63.1, C64.1, C65.1, C66.1, C67.1, C68.1, C69.1, C224.2, R49.2, R50.2, R51.2, R52.2, R53.2, R54.2, R55.2, R56.2, R57.2, R58.2, R59.2, R60.2, R61.2, R62.2, R63.2, R64.2, R65.2, R66.2, R67.2, R68.2, R69.2, R70.2, R71.2, R153.2, R167.2, U20.4 (VOUT)
FPGA_DONE: J18.4, Q3.1 (G), U1.F12 (DONE_0)
GND: A1.6 (GND), A1.7 (GND), A1.29 (GND), C1.1, C2.1, C3.2, C4.2, C5.1, C6.1, C7.1, C8.1, C9.1, C10.1, C11.1, C12.1, C13.1, C14.1, C15.1, C16.1, C17.1, C18.1, C19.1, C20.1, C21.1, C22.1, C23.1, C24.1, C25.1, C26.1, C27.1, C28.1, C29.1, C30.1, C31.1, C32.1, C33.1, C34.1, C35.1, C36.1, C37.1, C38.1, C39.1, C40.1, C41.1, C42.1, C43.1, C44.1, C45.1, C46.1, C47.1, C48.1, C49.2, C51.2, C52.2, C53.1, C61.1, C62.2, C63.2, C64.2, C65.2, C66.2, C67.2, C68.2, C69.2, C70.1, C71.2, C72.2, C73.2, C74.1, C75.1, C76.1, C77.1, C78.1, C79.1, C80.1, C81.1, C82.1, C83.1, C84.2, C85.1, C86.1, C87.1, C88.1, C89.1, C90.1, C91.1, C92.1, C93.1, C94.1, C95.1, C96.1, C97.1, C98.1, C99.1, C100.1, C101.1, C102.1, C103.1, C104.1, C105.1, C106.1, C107.1, C108.1, C109.1, C110.1, C111.1, C112.1, C113.1, C114.1, C115.1, C116.1, C117.1, C118.1, C119.1, C120.1, C121.1, C122.1, C123.1, C124.1, C125.1, C126.1, C127.1, C128.1, C129.1, C130.1, C131.1, C132.1, C133.1, C134.1, C135.1, C136.1, C137.1, C138.1, C139.1, C140.1, C141.1, C142.1, C143.1, C144.1, C145.1, C146.1, C147.1, C148.1, C149.1, C150.1, C152.1, C153.1, C155.1, C156.1, C157.1, C158.1, C159.1, C160.1, C161.1, C162.1, C163.1, C164.1, C165.1, C166.1, C167.1, C168.1, C169.1, C170.1, C171.1, C172.1, C173.1, C174.1, C175.1, C176.1, C177.1, C178.1, C179.1, C180.1, C181.1, C192.2, C195.2, C199.2, C200.2, C218.1, C219.1, C220.1, C221.1, C222.1, C223.1, C224.1, C225.1, C226.1, C227.1, C228.1, C229.1, C230.1, C231.1, C232.1, C233.1, C234.1, C235.1, C236.1, C237.1, C238.1, C239.1, C240.1, C241.1, C242.1, C243.1, C244.1, C245.1, C246.1, C249.1, C250.1, C255.1, C256.1, C257.1, C258.1, C259.1, C263.1, C264.1, D1.1 (GND), D6.2 (A), J1.1 (VEET), J1.10 (VEER), J1.11 (VEER), J1.14 (VEER), J1.17 (VEET), J1.20 (VEET), J2.A1 (GND), J2.A12 (GND), J2.B1 (GND), J2.B12 (GND), J2.S1 (SHIELD), J3.13 (LED1K), J3.15 (LED2K), J3.17 (SHIELD), J3.18 (SHIELD), J4.5, J4.11, J5.5, J5.11, J6.5, J6.11, J7.5, J7.11, J8.SH1 (CHASSIS_GND1), J8.SH2 (CHASSIS_GND1), J8.SH3 (CHASSIS_GND1), J8.SH4 (CHASSIS_GND1), J8.SH5 (CHASSIS_GND1), J8.SH6 (CHASSIS_GND1), J8.SH7 (CHASSIS_GND1), J8.SH8 (CHASSIS_GND1)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
GND_CRYSTAL: U13.4 (X1), U13.7 (X2), Y2.2 (GND), Y2.4 (GND)
I2C_SCL: J18.6, R140.1, TP2.1, U1.H17 (IO_L23P_T3_FOE_B_15), U3.4 (SCL), U12.7 (SCL), U17.19 (SCL), U19.19 (SCL), U26.12 (SCL), U28.6 (SCL)
I2C_SCL_Ardu: A1.14 (SCL/A5), A1.32 (SCL/A5), R84.2, U1.J18 (IO_L3P_T0_DQS_PUDC_B_14)
I2C_SDA: J18.5, R139.1, TP3.1, U1.F14 (IO_L22N_T3_A16_15), U3.3 (SDA), U12.6 (SDA), U17.20 (SDA), U19.20 (SDA), U26.13 (SDA), U28.5 (SDA)
I2C_SDA_Ardu: A1.13 (SDA/A4), A1.31 (SDA/A4), R141.1, U1.C12 (IO_L6N_T0_VREF_15)
JTAG_TCK: U1.F8 (TCK_0), U21.16 (ADBUS0)
JTAG_TDI: U1.T9 (TDI_0), U21.17 (ADBUS1)
JTAG_TDO: U1.T8 (TDO_0), U21.18 (ADBUS2)
JTAG_TMS: U1.R8 (TMS_0), U21.19 (ADBUS3)
LED0: Q1.1 (G), R156.2, U17.16
LED1: Q2.1 (G), R158.2, U17.17
MDC_PHY: U1.H14 (IO_25_15), U7.13 (MDC)
MDIO_PHY: R182.1, U1.E18 (IO_L24N_T3_RS0_15), U7.14 (MDIO)
MGT_RX0_N: J12.12 (RD-), U1.E3 (MGTPRXN0_216)
MGT_RX0_P: J12.13 (RD+), U1.E4 (MGTPRXP0_216)
MGT_RX1_N: J1.12 (RD-), U1.A3 (MGTPRXN1_216)
MGT_RX1_P: J1.13 (RD+), U1.A4 (MGTPRXP1_216)
MGT_RX2_N: J11.12 (RD-), U1.C3 (MGTPRXN2_216)
MGT_RX2_P: J11.13 (RD+), U1.C4 (MGTPRXP2_216)
MGT_RX3_N: J13.12 (RD-), U1.G3 (MGTPRXN3_216)
MGT_RX3_P: J13.13 (RD+), U1.G4 (MGTPRXP3_216)
MGT_TX0_N: J12.19 (TD-), U1.H1 (MGTPTXN0_216)
MGT_TX0_P: J12.18 (TD+), U1.H2 (MGTPTXP0_216)
MGT_TX1_N: J1.19 (TD-), U1.F1 (MGTPTXN1_216)
MGT_TX1_P: J1.18 (TD+), U1.F2 (MGTPTXP1_216)
MGT_TX2_N: J11.19 (TD-), U1.D1 (MGTPTXN2_216)
MGT_TX2_P: J11.18 (TD+), U1.D2 (MGTPTXP2_216)
MGT_TX3_N: J13.19 (TD-), U1.B1 (MGTPTXN3_216)
MGT_TX3_P: J13.18 (TD+), U1.B2 (MGTPTXP3_216)
unnamed: C50.2, R103.2, R104.2
unnamed: C52.1, R103.1
unnamed: C192.1, C195.1, L17.2, L18.1
unnamed: D2.2 (A), Q4.4 (G), R152.2
unnamed: D3.2 (A), R154.2, TP14.1, U24.2 (IN), U25.2 (IN)
unnamed: D3.1 (K), TP6.1, U6.5 (PG), U11.5 (PG), U23.6 (PG)
unnamed: D5.1 (K), J18.2
unnamed: D6.1 (K), LD1.1 (C)
unnamed: C27.2, C29.2, J1.15 (VCCR), L4.2
unnamed: C28.2, C30.2, J1.16 (VCCT), L5.2
unnamed: J3.14 (LED1A), R20.2
unnamed: J3.16 (LED2A), R19.2
unnamed: C16.2, J3.1 (TRCT3), J3.6 (TRCT2), J3.7 (TRCT4), J3.12 (TRCT1)
unnamed: C35.2, C39.2, J11.15 (VCCR), L6.2
unnamed: C36.2, C40.2, J11.16 (VCCT), L7.2
unnamed: C19.2, C20.2, J12.15 (VCCR), L2.2
unnamed: C23.2, C24.2, J12.16 (VCCT), L3.2
unnamed: C37.2, C41.2, J13.15 (VCCR), L8.2
unnamed: C38.2, C42.2, J13.16 (VCCT), L9.2
unnamed: J14.1, R187.2
unnamed: J14.2, R188.2
unnamed: J14.3, R189.2
unnamed: J14.4, R190.2
unnamed: J14.7, R191.1
unnamed: J14.8, R197.1
unnamed: J14.9, R198.1
unnamed: J14.10, R199.1
unnamed: J15.1, R118.2
unnamed: J15.2, R119.2
unnamed: J15.3, R147.2
unnamed: J15.4, R173.2
unnamed: J15.7, R174.1
unnamed: J15.8, R176.1
unnamed: J15.9, R185.1
unnamed: J15.10, R186.1
unnamed: J16.1 (In), R104.1
unnamed: JP1.1 (A), R183.1, U12.8 (VSET)
unnamed: JP2.1 (A), R183.2
unnamed: JP3.1 (A), R184.1, U12.9 (ISET)
unnamed: JP4.1 (A), R184.2
unnamed: LD1.2 (A), R111.1, R112.1
unnamed: LD2.2 (A), R148.1, U25.4 (OUT)
unnamed: LD3.2 (A), R155.1
unnamed: LD3.1 (C), Q1.3 (D)
unnamed: LD4.2 (A), R157.1
unnamed: LD4.1 (C), Q2.3 (D)
unnamed: LD5.2 (A), R161.1
unnamed: LD5.1 (C), Q3.3 (D)
unnamed: J10.1, Q4.5 (D)
unnamed: Q5.4 (G), R80.2, R82.2, R192.2, R193.2
unnamed: Q7.3 (D), R99.1, Y1.1 (INH)
unnamed: R123.1, R125.2, R126.1
unnamed: R127.2, R128.1, R129.1
unnamed: R131.2, R132.1, R133.1
unnamed: R135.2, R136.1, R137.1
unnamed: R196.2, SW3.1
unnamed: R114.1, U1.A6 (MGTRREF_216)
unnamed: R86.1, U1.E12 (CFGBVS_0)
unnamed: R87.1, U1.T10 (INIT_B_0)
unnamed: R88.1, U1.R12 (M0_0)
unnamed: R89.2, U1.R11 (M1_0)
unnamed: R90.2, U1.F13 (M2_0)
unnamed: C155.2, L16.2, U1.J10 (VCCADC_0)
unnamed: R72.1, U2.L8 (ZQ)
unnamed: R142.1, R177.2, U4.6 (EN)
unnamed: R1.1, R2.2, U4.7 (FB)
unnamed: R143.1, R178.2, U4.5 (PG), U5.6 (EN)
unnamed: R95.1, R96.2, R97.2, U5.7 (FB)
unnamed: C179.2, R91.1, R92.1, R196.1, U6.7 (FB)
unnamed: TP4.1, U7.31 (INTB/PMEB)
unnamed: L1.1, U7.30 (REG_OUT)
unnamed: R3.1, U7.39 (RSET)
unnamed: C4.1, R160.2, U7.36 (XTAL_IN), Y4.1 (X)
unnamed: C3.1, C247.1, U7.37 (XTAL_OUT/EXT_CLK), Y4.3 (X)
unnamed: C81.2, L12.2, U8.1 (EN), U8.4 (VIN)
unnamed: R81.1, R83.1, U8.5 (FB)
unnamed: L14.1, U8.3 (SW)
unnamed: C152.2, C153.2, L15.2, U9.1 (IN)
unnamed: R144.1, R145.1, R179.2, R180.2, U5.5 (PG), U10.6 (EN), U11.6 (EN)
unnamed: C178.2, R93.1, R94.2, U10.7 (FB)
unnamed: R146.1, R181.2, U6.6 (EN), U10.5 (PG)
unnamed: R98.2, R100.1, R101.1, R169.2, U11.7 (FB)
unnamed: R192.1, R193.1, U12.10 (GATE)
unnamed: R194.1, R195.1, U12.1 (VIN)
unnamed: C50.1, U13.43 (IN0)
unnamed: R159.1, U13.25 (OUT1)
unnamed: R115.1, U13.31 (OUT2)
unnamed: U13.5 (XA), Y2.3 (X)
unnamed: U13.6 (XB), Y2.1 (X)
unnamed: C51.1, U13.44 (~IN0)
unnamed: R164.2, U17.6 (P05)
unnamed: R165.2, U17.7 (P06)
unnamed: R166.2, U17.8 (P07)
unnamed: R170.2, U19.6 (P05)
unnamed: R171.2, U19.7 (P06)
unnamed: R172.2, U19.8 (P07)
unnamed: R175.2, U19.17
unnamed: R77.1, U21.62 (EECLK), U22.2 (CLK)
unnamed: R76.1, U21.63 (EECS), U22.1 (CS)
unnamed: R74.2, U21.61 (EEDATA), U22.3 (DI)
unnamed: C72.1, U21.2 (OSCI), Y5.2 (OSC2)
unnamed: C71.1, U21.3 (OSCO), Y5.1 (OSC1)
unnamed: R78.2, U21.6 (REF)
unnamed: R79.1, U21.14 (RESET#)
unnamed: C85.2, C86.2, L10.2, U21.4 (VPHY)
unnamed: C87.2, C88.2, L13.2, U21.9 (VPLL)
unnamed: R74.1, R75.2, U22.4 (DO)
unnamed: SW1.2, U27.9 (~WP/IO2)
unnamed: R117.1, Y1.3 (CLK)
PHY_RSTn: U1.A13 (IO_L8P_T1_AD10P_15), U7.12 (PHYRSTB)
PMOD1_1_N: J4.2, U1.V13 (IO_L21N_T3_DQS_A06_D22_14)
PMOD1_1_P: J4.1, U1.V12 (IO_L21P_T3_DQS_14)
PMOD1_2_N: J4.4, U1.V11 (IO_L23N_T3_A02_D18_14)
PMOD1_2_P: J4.3, U1.U11 (IO_L23P_T3_A03_D19_14)
PMOD1_3_N: J4.8, U1.U12 (IO_L22N_T3_A04_D20_14)
PMOD1_3_P: J4.7, U1.T12 (IO_L22P_T3_A05_D21_14)
PMOD1_4_N: J4.10, U1.V9 (IO_L24N_T3_A00_D16_14)
PMOD1_4_P: J4.9, U1.U9 (IO_L24P_T3_A01_D17_14)
PMOD2_1_N: J5.2, U1.V14 (IO_L20N_T3_A07_D23_14)
PMOD2_1_P: J5.1, U1.U14 (IO_L20P_T3_A08_D24_14)
PMOD2_2_N: J5.4, U1.U17 (IO_L16N_T2_A15_D31_14)
PMOD2_2_P: J5.3, U1.T17 (IO_L16P_T2_CSI_B_14)
PMOD2_3_N: J5.8, U1.V17 (IO_L18N_T2_A11_D27_14)
PMOD2_3_P: J5.7, U1.V16 (IO_L18P_T2_A12_D28_14)
PMOD2_4_N: J5.10, U1.U16 (IO_L17N_T2_A13_D29_14)
PMOD2_4_P: J5.9, U1.U15 (IO_L17P_T2_A14_D30_14)
PMOD3_1_N: J6.2, U1.P16 (IO_L11N_T1_SRCC_14)
PMOD3_1_P: J6.1, U1.P15 (IO_L11P_T1_SRCC_14)
PMOD3_2_N: J6.4, U1.T18 (IO_L15N_T2_DQS_DOUT_CSO_B_14)
PMOD3_2_P: J6.3, U1.R18 (IO_L15P_T2_DQS_RDWR_B_14)
PMOD3_3_N: J6.8, U1.R17 (IO_L14N_T2_SRCC_14)
PMOD3_3_P: J6.7, U1.R16 (IO_L14P_T2_SRCC_14)
PMOD3_4_N: J6.10, U1.N14 (IO_L8N_T1_D12_14)
PMOD3_4_P: J6.9, U1.M14 (IO_L8P_T1_D11_14)
PMOD4_1_N: J7.2, U1.J16 (IO_L2N_T0_D03_14)
PMOD4_1_P: J7.1, U1.J15 (IO_L2P_T0_D02_14)
PMOD4_2_N: J7.4, U1.K15 (IO_L5N_T0_D07_14)
PMOD4_2_P: J7.3, U1.J14 (IO_L5P_T0_D06_14)
PMOD4_3_N: J7.8, U1.L18 (IO_L4N_T0_D05_14)
PMOD4_3_P: J7.7, U1.K17 (IO_L4P_T0_D04_14)
PMOD4_4_N: J7.10, U1.M17 (IO_L7N_T1_D10_14)
PMOD4_4_P: J7.9, U1.M16 (IO_L7P_T1_D09_14)
PMOD5_0: R187.1, U1.M15 (IO_L6N_T0_D08_VREF_14)
PMOD5_1: R188.1, U1.K18 (IO_L3N_T0_DQS_EMCCLK_14)
PMOD5_2: R189.1, U1.N16 (IO_L9P_T1_DQS_14)
PMOD5_3: R190.1, U1.P18 (IO_L10N_T1_D15_14)
PMOD5_4: R191.2, U1.N18 (IO_L10P_T1_D14_14)
PMOD5_5: R197.2, U1.G15 (IO_L21P_T3_DQS_15)
PMOD5_6: R198.2, U1.F15 (IO_L21N_T3_DQS_A18_15)
PMOD5_7: R199.2, U1.N17 (IO_L9N_T1_DQS_D13_14)
PMOD6_0: J17.2 (DAT3/CD), R106.2, R118.1, U1.T13 (IO_L19N_T3_A09_D25_VREF_14)
PMOD6_1: J17.3 (CMD), R107.2, R119.1, U1.U10 (IO_25_14)
PMOD6_2: J17.7 (DAT0), R109.2, R147.1, U1.R13 (IO_L19P_T3_A10_D26_14)
PMOD6_3: J17.5 (CLK), R108.2, R173.1, U1.T14 (IO_L13P_T2_MRCC_14)
PMOD6_4: J17.8 (DAT1), R110.2, R174.2, U1.T15 (IO_L13N_T2_MRCC_14)
PMOD6_5: J17.1 (DAT2), R105.2, R176.2, U1.P14 (IO_L12P_T1_MRCC_14)
PMOD6_6: R185.2, U1.L14 (IO_0_14)
PMOD6_7: R186.2, U1.R15 (IO_L12N_T1_MRCC_14)
REF_CLK0_N: C214.1, U1.B5 (MGTREFCLK1N_216)
REF_CLK0_P: C204.1, U1.B6 (MGTREFCLK1P_216)
REG_1V0: C11.2, C12.2, C13.2, C14.2, C15.2, C17.2, C18.2, L1.2, U7.3 (AVDD10), U7.8 (AVDD10), U7.21 (DVDD10), U7.38 (AVDD10)
RGMII_RXD0: R4.1, U1.B16 (IO_L15P_T2_DQS_15)
RGMII_RXD1: R5.1, U1.C16 (IO_L16P_T2_A28_15)
RGMII_RXD2: R6.1, U1.D14 (IO_L12N_T1_MRCC_15)
RGMII_RXD3: R7.1, U1.C13 (IO_L11N_T1_SRCC_15)
RGMII_RX_CLK: R8.1, U1.E13 (IO_L12P_T1_MRCC_15)
RGMII_RX_DV: R9.1, U1.D16 (IO_L14N_T2_SRCC_15)
RGMII_TXD0: U1.B17 (IO_L16N_T2_A27_15), U7.18 (TXD0)
RGMII_TXD1: U1.E16 (IO_L14P_T2_SRCC_15), U7.17 (TXD1)
RGMII_TXD2: U1.E17 (IO_L17P_T2_A26_15), U7.16 (TXD2)
RGMII_TXD3: U1.D18 (IO_L17N_T2_A25_15), U7.15 (TXD3)
RGMII_TX_CLK: U1.D15 (IO_L13N_T2_MRCC_15), U7.20 (TXC)
RGMII_TX_EN: U1.A17 (IO_L15N_T2_DQS_ADV_B_15), U7.19 (TXCTL)
RST: D5.2 (A), R85.1, R122.1, TP5.1, U1.P10 (PROGRAM_B_0), U24.4 (OUT), U26.1 (~RESET)
RTS: SW2.2, U21.40 (BDBUS2)
RX: U1.F17 (IO_L24P_T3_RS1_15), U21.39 (BDBUS1)
TX: U1.H18 (IO_L23N_T3_FWE_B_15), U21.38 (BDBUS0)
VCC_IN: D2.1 (C), D4.1 (K), Q4.1 (S), Q4.2 (S), Q4.3 (S), R113.1, U3.8 (VIN+)
VCC_USB: C45.2, C46.2, D4.2 (A), Q5.5 (D)
VUSB: D1.4 (VCC), J2.A4 (VBUS), J2.A9 (VBUS), J2.B4 (VBUS), J2.B9 (VBUS), L12.1, Q5.1 (S), Q5.2 (S), Q5.3 (S), R80.1, R82.1, R194.2, R195.2
WR_CLK0_N: C213.1, U1.D5 (MGTREFCLK0N_216)
WR_CLK0_P: C205.1, U1.D6 (MGTREFCLK0P_216)
WR_CLK.RSTN: U13.17 (~RST), U19.15
WR_CLK.SI5340_IRQ_N: U13.33 (~INTR), U17.15
WR_DAC1_SYNC: U1.D11 (IO_L6P_T0_15), U13.16 (A0/~CS)
WR_DAC2_SYNC: U1.D10 (IO_0_15), U13.13 (SDA/SDIO)
WR_DAC_DIN: U1.B11 (IO_L4N_T0_15), U13.15 (A1/SDO)
WR_DAC_SCLK: U1.C11 (IO_L4P_T0_15), U13.14 (SCLK)
XADCGND: C151.1, C154.1, L11.2, U1.J9 (GNDADC_0), U1.K9 (VREFN_0), U1.K10 (VP_0), U1.L9 (VN_0), U9.3 (GND)

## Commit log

2024-11-05 Devel
2024-11-12 Adding a few suggestions
2024-11-19 README.md: Number of PMOD ports updated
2024-11-20 Add more details about pins
2025-02-06 first
2025-03-27 components placement and PCB routing
2025-04-17 PCB done
2025-04-18 corrected location of pmod connectors
2025-04-25 connected more address lines to DDR, new board name
2025-05-22 ready for the final review
2025-06-12 changed name in readme
2025-09-30 license.txt: CERN OHL P 2.0 license agreement file added
2025-09-30 README.md: copyright notice added
2025-10-08 license.txt: switch from CERN-OHL-P-2.0 to CERN-OHL-W-2.0 license
2025-10-08 COPYRIGHT.md: new file added
2025-10-09 COPYRIGHT.md: fix typo in the file name
2025-12-30 Removing unnecessary components for the interface. Adding SPIN schematic and footprint
2025-12-30 adding SPIN, and 5V power for the MCU
2026-01-23 update with available components on LCSC
2026-01-26 adding wago
2026-01-27 replacing global label with hierarchical label
2026-01-27 correcting SFP cages footprint
2026-01-27 adding new netclass for DDR memory
2026-01-29 Adding symbol library
2026-01-30 Correct Schematic errors
2026-01-30 correcting mismatch in TX/RX of UART
2026-02-09 adding 3D files, 3D model of twist, and correct DRC
2026-02-10 update pcb
2026-02-10 Changed layout in a way TWIST and Obsidian are aligned properly.
2026-02-10 adding a standoff 30mm for TWIST mechanical connection
2026-02-11 revison v1.1.0 ready to review
2026-02-11 updated 3D render
2026-02-13 adding pogo pins in the 3D model
2026-02-17 adding flex connector
2026-02-20 Cleanup of the schematic
2026-02-20 replacing footprint of the mouting hole to have pad top only
2026-02-21 Adding return vias for SPI
2026-02-21 correcting via position for SERDES transceiver
2026-02-21 correcting some footprint issues
2026-02-21 Solving DRC errors
2026-02-21 solving skew error of MGT tracks
2026-02-22 adding VIA return for clock tracks
2026-02-22 solving DRC issues on the PCB
2026-03-02 cleaning pcb
2026-03-02 cleaning schematic
2026-03-11 correct SN74LVC1G07DBV floating pins
2026-03-11 deleting two labels on 1V net, replacing with VCCINT_1V
2026-03-11 check USB serial signals : Continuous plane OK, ground via whenever possible
2026-03-11 Checking USB dbg
    - Return gorund via placed whenever possible
    - TDI and TDO OK
    - TCK ground is cut by a 12V line
    - TMS seems cut by VCCINT plane, but is not considered as a fast signal
2026-03-11 solving issues of USB debug signal being pulled
2026-03-12 adding return vias for CLK WR
2026-03-12 minor changes
2026-03-12 new 3D render
2026-03-12 Checking impedance matching for SPI
2026-03-12 correct datasheet for LD3900PU12RY U23 components
2026-03-12 Making standoff 3D model visible
2026-03-12 updating 3D step of easyEDA imported files
2026-03-13 moving flex pins for SCIN and SCK from PA13/PA14 to PC8/PC9
2026-03-13 replacing FH 0402CG270J500NT capacitor for XTAL in USB with CL05C330JB5NNNC
2026-03-13 adding netclass for I2C, adding return GND vias whenever possible
2026-03-13 Removing 12V track
2026-03-13 correcting straightness of kicad plane around 1V2 regulator
2026-03-13 adding return GND for quad-spi flash
2026-03-13 Making the standoff appearing again
2026-03-13 Update standoff 3d model
2026-03-13 removing reset global label
2026-03-23 new LBL logo
2026-03-24 Reconnecting 12V pins
2026-03-26 add wire after PHY as RGMII classnet
2026-03-28 adding 1V regulator for MGT transceiver
2026-03-29 Modifying line voltage for certain components, adding pull up resistor
2026-03-29 adding capacitor filter for reset pins
2026-03-29 adding lcsc reference for PMOD
2026-03-29 update LCSC reference, and OFFSET rotation for JLCPCB
2026-03-30 Replacing oscillators with CMOS output oscillator
2026-03-30 Update the components around U16, see #9
2026-03-31 adding production files, and documentations
2026-04-02 update ethernet LCSC components
2026-04-07 new font; removed clk gen; added resistors for 2 PMODs
2026-04-07 Ignore Fabrication folder
2026-04-07 removed Fabrication folder
2026-04-16 Adding documentation for configuration with flash memory, adding more comments to schematic
2026-04-17 Update the documentation
2026-04-17 routing U19 on the top, feeback resistor close to delivery point
2026-04-20 adding comments, and test point for U12 (power supply in clock sheet)
2026-04-20 adding LVCMOS conversiont circuit
2026-04-20 adding LVCMOS conversion circuit in PCB
2026-04-20 mermaid of of power tree
2026-04-23 adding test procedure
2026-04-24 adding meanders to clock signal
2026-04-24 adding test pins for DAC, and clock
2026-04-24 Putting back S25FL128SAGMFI001 in FPGA_DBG sheet, see #17
2026-05-04 ready to manufacture
2026-05-06 adding some modifications
2026-05-06 updating silkscreen with kibuzard
2026-05-07 Update TPSM863257RDXR symbol to set output pins as output power. Putting pull-up resistor on flash spi, decoupling capacitor and deconnect Vio.
2026-05-07 Adding power estimation table in power sheet
2026-05-07 Regenerate production files
2026-05-07 Replace ascii table in kicad with true table, correct footprint of SFP cages. Correct DRC warning : remove unconnected track and via.
2026-05-18 Cleaning symbol fields
2026-05-18 cleaning zone around 93LC46B_SN (U22) in USB sheet
2026-05-18 Separating auxiliary clock from WR clock
2026-05-19 Update PCB to solve routing issues
2026-05-19 Clean symbol fields
2026-05-19 Adding SFP dongle as DNP
2026-05-22 adding resistor in SFP sheep for SFP/SFP+ compatibility
2026-06-01 Adding the gnd shield
2026-06-01 Adding local datasheet to the repo
2026-06-01 putting input resistor/capacitor of U3 in DNP (see #29)
2026-06-02 Changed the layout so that we have guard rails. Changed USB and RJ45 position Changed Flex connector position. Changed flash LDO position Improved silkscreen. Changed outline around RJ45. Changed SFP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
2026-06-08 Update the schematic, PCB
    - Cleaning silkcreen
    - Solving uncoupled length issues
    - Solving unfound footprint issues
2026-06-08 Update schematic for out of stock components
2026-06-08 Replacing C203, C210 footprint
2026-06-08 Update PCB routing for LDO regulator
2026-06-08 Correct offset and position on JLCPCB, re-generate production folder
2026-06-08 Adding informations about I2C address, and PCB stackup
2026-06-08 correct stackupt png
2026-06-10 As ordered 10/06/26

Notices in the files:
parts and their libraries:
License: CC-BY-SA 4.0
